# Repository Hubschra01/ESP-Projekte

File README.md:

# ESP-Projekte
ESP8266 / ESP32 Projekte for Home Assistant

This is a collection of my projects for the ESP8266 and ESP 32 in connection with the smart home with home assistant that I use.

I take no responsibility for the function of the projects. 
These modules, some of which I built myself, work in my smart home environment.

Reproduction and use are at your own risk

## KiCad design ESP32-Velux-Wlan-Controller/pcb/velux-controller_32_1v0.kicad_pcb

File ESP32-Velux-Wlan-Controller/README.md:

# Velux-ESP32-RemoteController
ESP32 WlanController for Velux KLI 310 Remotecontroller to integrate it into Smarthome like Home Assistant with ESP Home.

This WLan Controller for Velux KLI310 Switch is based on this GitHub Projekt form thorio https://github.com/thorio/esphome-projects/tree/master/velux-controller.

I did a workaround and use an ESP32 controller instead of an ESP8266 (ESP-12F) module.

This board also features an IIC bus socket for connecting a small sensor board to the ESP-32.
I use it with a BME280 module like this 

to transfer the sensor data to Home Assistant

All you need to do is carefully remove the plastic back of the KLI switch and solder 5 wires to the board.

Two wires supplies the KLI board with 3.3V instead of the batteries.
The other 3 wires are for up, stop and down command.

The Voltagesupply is an 5V USB Smartphone Charger

Partlist:

- 1   CLIFF FC68148S     Einbaukupplung SMD, 6,4 x 2,1 mm
- 2   TPS 3216 22/6,3    MD-Tantal Kondensator, 22µF, 6,3V
- 2   TASTER 3301        Kurzhubtaster 6x6mm, Höhe: 4,3mm, 12V, vertikal
- 1   LM 1117 IMP-3.3    LDO-Spannungsregler, fix, 3,3 V, 800mA, SOT-223
- 1   KEM X5R0805 10U    Vielschicht-Kerko, 10µF, 10V, 85°C
- 2   WAL 0805B104K500   SMD-Kerko, 0805, 100 nF, 50V, 10%, X7R, MLCC
- 1   ESP32WROOM32E      WIFI-SMD-Modul, ESP32-D0WD-V3, 4 MB SPI, 3,3 V, 18 x 25,5 x 3,1
- 3   MMBT 3904LT1G      Bipolartransistor, NPN, 40V, 0,2A, 0,225W, SOT-23
- 1   M-A 470U 6,3       Elko, radial, 470 µF, 6,3 V, RM 2,5, 85°C, 2000h, 20%
- 1   SM 10/16RAD        Subminiatur-Elko, radial, 10 µF, 16 V, RM 1,5, 85°C, 1000h, 20%
- 8   WAL WR08X1001FTL   SMD-Widerstand, 0805, 1 kOhm, 125 mW, 1%
- 5   WAL WR08X1002FTL   SMD-Widerstand, 0805, 10 kOhm, 125 mW, 1%
- 1   JST XH3P ST90      JST - Stiftleiste, 90°, 1x3-polig - XH
- 1   JST XH2P ST90      JST - Stiftleiste, 90°, 1x2-polig - XH
- 1   W+P 946-124        Stiftleiste RM 2,54mm, gewinkelt, 1-reihig, 4-polig
- 1   MPE 087-1-004      Stiftleisten 2,54 mm, 1X04, gerade
- 1   DELOCK 82197       USB Konverter, A Stecker auf 1x Hohlstecker, 1 m

Firmware:
code.yaml

Thanks to:

https://github.com/thorio/esphome-projects/tree/master/velux-controller

Disclaimer:

Any reconstruction and operation of the Hardware, PCB and Software is at your own risk.

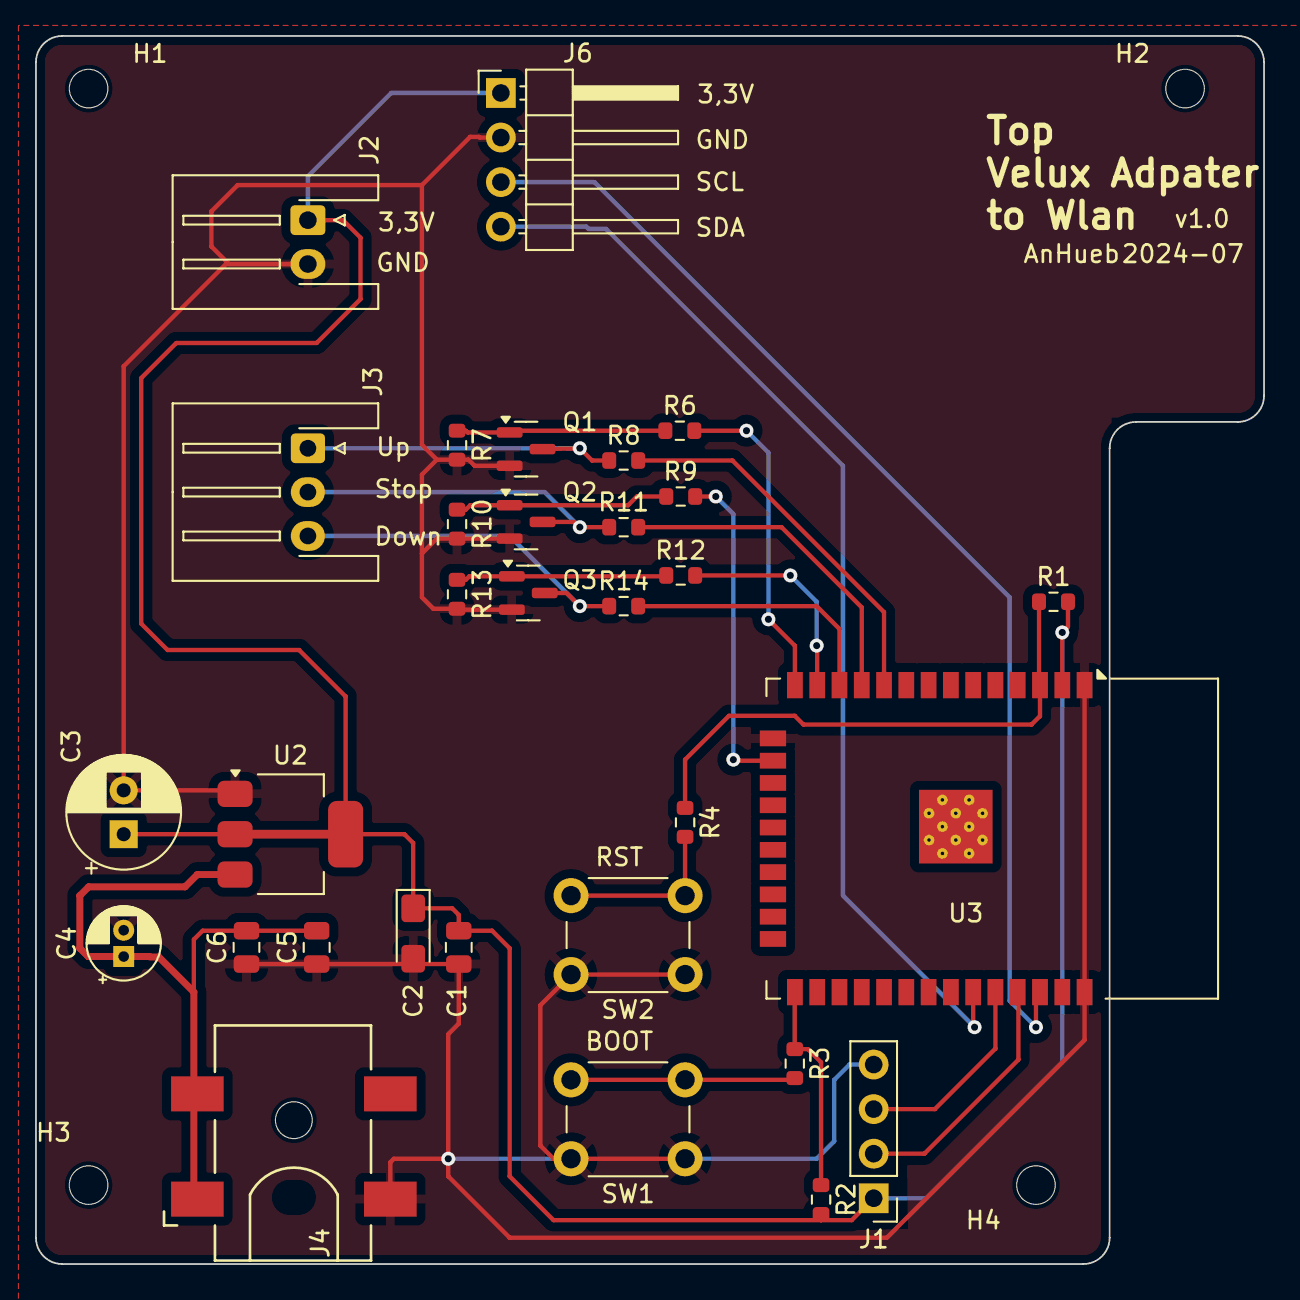
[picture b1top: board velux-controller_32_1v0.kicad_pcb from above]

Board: 2 copper layers, 70.0 x 70.0 mm, 35 parts (0 on the bottom side), 23 nets.

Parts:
C1, C6: 0.1μF; C_0805_2012Metric
C2: 22μF; CP_EIA-3216-10_Kemet-I_Pad1.58x1.35mm_HandSolder
C3: 470μF; CP_Radial_D6.3mm_P2.50mm
C4: 10μF; CP_Radial_D4.0mm_P1.50mm
C5: 10μF; C_0805_2012Metric
H1, H2, H3, H4: MountingHole; MountingHole_2.2mm_M2
J1: UART; PinHeader_1x04_P2.54mm_Vertical
J2: POWER; JST_XH_S2B-XH-A-1_1x02_P2.50mm_Horizontal
J3: SIGNAL; JST_XH_S3B-XH-A-1_1x03_P2.50mm_Horizontal
J4: PWR; BarrelJack_CLIFF_...8S_SMT_Horizontal
J6: IIC_Bus; PinHeader_1x04_P2.54mm_Horizontal
Q1, Q2, Q3: MMBT3904; SOT-23
R1, R2, R7, R10, R13: 10K; R_0603_1608Metric
R3: 1k; R_0603_1608Metric
R4, R6, R8, R9, R11, R12, R14: 1K; R_0603_1608Metric
SW1: BOOT; SW_PUSH_6mm_H4.3mm
SW2: RST; SW_PUSH_6mm_H4.3mm
U2: AMS1117-3.3; SOT-223-3_TabPin2
U3: ESP32-WROOM-32

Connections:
+3.3V: C1.2, C2.1, C3.1, J1.1, J2.1, J6.1, R1.2, R2.2, U2.2 (VO), U3.2 (VDD)
/EN: R1.1, R4.1, U3.3 (EN)
/GPIO0: R2.1, R3.1, U3.25 (IO0)
/GPIO12: R6.2, U3.14 (IO12)
/GPIO13: R9.2, U3.16 (IO13)
/GPIO14: R12.2, U3.13 (IO14)
/GPIO25: R8.2, U3.10 (IO25)
/GPIO26: R11.2, U3.11 (IO26)
/GPIO27: R14.2, U3.12 (IO27)
/IIC_SCL: J6.3, U3.36 (IO22)
/IIC_SDA: J6.4, U3.33 (IO21)
/LINE_DOWN: J3.1, Q1.3 (C), R8.1
/LINE_STOP: J3.2, Q2.3 (C), R11.1
/LINE_UP: J3.3, Q3.3 (C), R14.1
/RXD: J1.3, U3.34 (RXD0/IO3)
/TXD: J1.2, U3.35 (TXD0/IO1)
GND: C1.1, C2.2, C3.2, C4.2, C5.1, C6.1, J1.4, J2.2, J4.3, J6.2, Q1.2 (E), Q2.2 (E), Q3.2 (E), R7.2, R10.2, R13.2, SW1.1, SW2.1, U2.1 (GND), U3.1 (GND), U3.15 (GND), U3.38 (GND)
unnamed: Q1.1 (B), R6.1, R7.1
unnamed: Q2.1 (B), R9.1, R10.1
unnamed: Q3.1 (B), R12.1, R13.1
unnamed: R3.2, SW1.2
unnamed: R4.2, SW2.2
VCC: C4.1, C5.2, C6.2, J4.1, U2.3 (VI)

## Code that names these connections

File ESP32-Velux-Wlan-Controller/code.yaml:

esphome:
  name: esphome-web-8b7918
  friendly_name: Room

esp32:
  board: esp32dev
  framework:
    type: arduino

# Enable logging
logger:

# Enable Home Assistant API
api:
  encryption:
    key: "Your Key"

# webserver
web_server:

# OTA
ota:
  platform: esphome
  password: "Your Password"


wifi:
  ssid: !secret wifi_ssid
  password: !secret wifi_password

  # Enable fallback hotspot (captive portal) in case wifi connection fails
  ap:
    ssid: "Esphome-Web-8B7918"
    password: "XrWH670zkeUH"

captive_portal:
  
i2c:
  sda: GPIO21
  scl: GPIO22
  scan: true
  id: bus_a    



# We can't use buttons and outputs, because we need to be able to
# read the output's state for the input filtering below.
switch:
  - platform: gpio
    id: output_up
    pin: GPIO14
    on_turn_on:
      then:
        - delay: 200ms
        - switch.turn_off: output_up
  - platform: gpio
    id: output_stop
    pin: GPIO13
    on_turn_on:
      then:
        - delay: 200ms
        - switch.turn_off: output_stop
  - platform: gpio
    id: output_down
    pin: GPIO12
    on_turn_on:
      then:
        - delay: 200ms
        - switch.turn_off: output_down

# These pins are connected to the output, and will be low if either:
# - We set the output pins
# - Someone presses the physical buttons on the original remote
#
# To avoid interference from ourselves, we ignore the input pins
# if we're the ones driving the output low.
binary_sensor:
  - platform: gpio
    id: sense_up
    pin: GPIO27
    filters:
      - lambda: !lambda return !(x || id(output_up).state);
    on_press:
      then:
        - cover.open: shutters
  - platform: gpio
    id: sense_stop
    pin: GPIO26
    filters:
      - lambda: !lambda return !(x || id(output_stop).state);
    on_press:
      then:
        - cover.stop: shutters
  - platform: gpio
    id: sense_down
    pin: GPIO25
    filters:
      - lambda: !lambda return !(x || id(output_down).state);
    on_press:
      then:
        - cover.close: shutters

cover:
  - platform: time_based
    id: shutters
    name: Window Shutters
    has_built_in_endstop: true
    manual_control: true
    assumed_state: true

    open_action:
      - switch.turn_on: output_up
    open_duration: 35s # measure this

    close_action:
      - switch.turn_on: output_down
    close_duration: 35s # measure this

    stop_action:
      - switch.turn_on: output_stop

sensor:
  - platform: bme280_i2c
    temperature:
     name: "BME280 Temperature"
    pressure:
     name: "BME280 Pressure"
    humidity:
     name: "BME280 Humidity"
    address: 0x76
    update_interval: 120s
